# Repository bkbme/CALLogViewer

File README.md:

CALLogViewer
============

A remote logviewer.

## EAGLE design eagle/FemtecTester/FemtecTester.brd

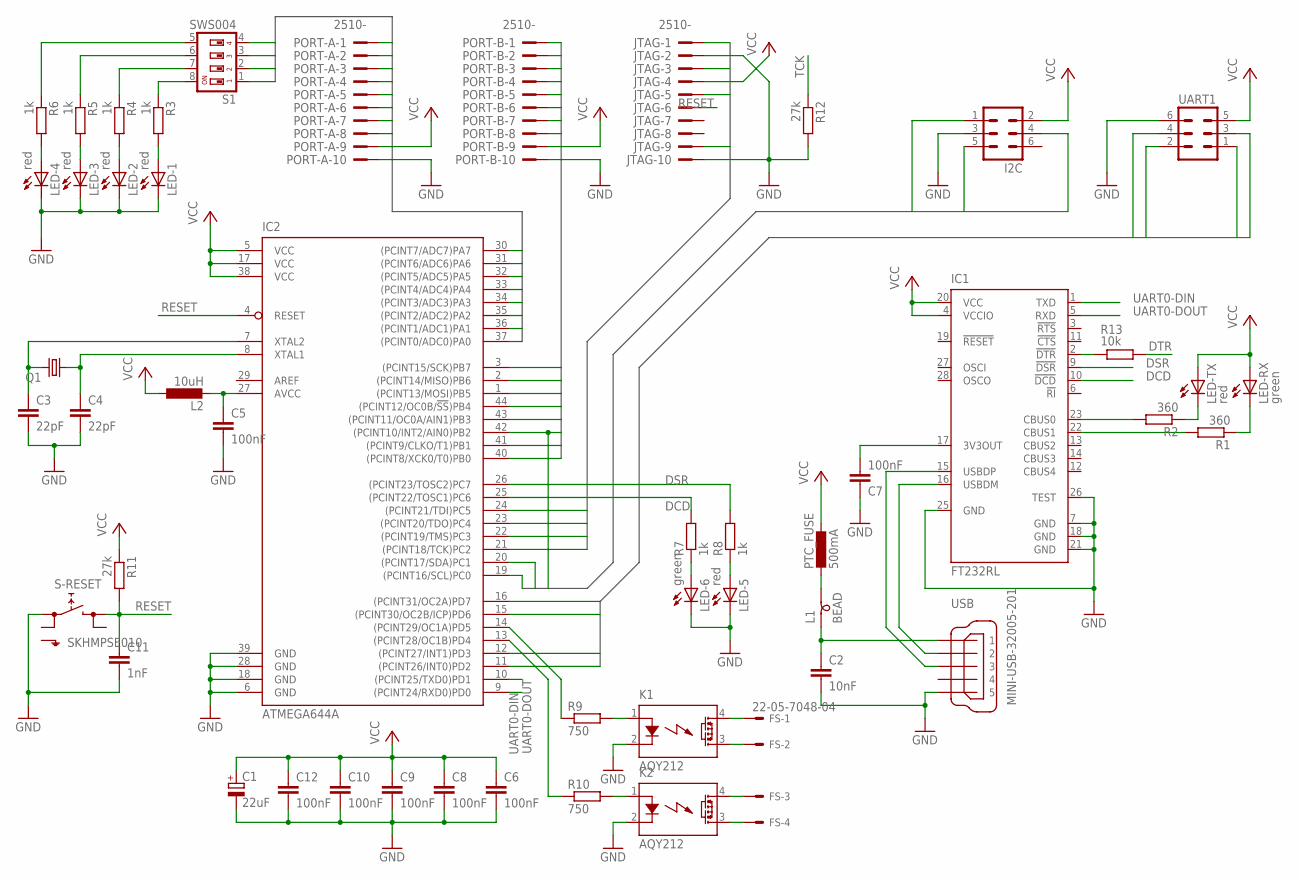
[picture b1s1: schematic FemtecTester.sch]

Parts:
C1: 22uF; SMC_D
C2: 10nF; C1206K
C3, C4: 22pF; C1206K
C5, C6, C7, C8, C9, C10, C12: 100nF; C1206K
C11: 1nF; C1206K
FS: 22-05-7048-04; 7395-04
I2C: ML6
IC1: FT232RL; SSOP28
IC2: ATMEGA644A; TQFP44
JTAG: 2510-; PAK100/2500-10
K1, K2: AQY212; SMD-DIP04
L1: BEAD; SM-B9
L2: 10uH; L3230M
LED-1, LED-2, LED-3, LED-4, LED-5: red; CHIPLED_1206
LED-6: green; CHIPLED_1206
LED-RX: green; CHIPLED_1206
LED-TX: red; CHIPLED_1206
PORT-A: 2510-; PAK100/2500-10
PORT-B: 2510-; PAK100/2500-10
PTC_FUSE: 500mA; L1812
Q1: CRYSTALHC49UP; HC49UP
R1, R2: 360; M1206
R3, R4, R5, R6, R7, R8: 1k; M1206
R9, R10: 750; M1206
R11, R12: 27k; M1206
R13: 10k; M1206
S1: SWS004; SMS-004
S-RESET: SKHMPSE010; SKHMPXE010
UART1: ML6
USB: MINI-USB-32005-201; 32005-201

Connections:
A0: IC2.37 ((PCINT0/ADC0)PA0), PORT-A.1
A1: IC2.36 ((PCINT1/ADC1)PA1), PORT-A.2
A2: IC2.35 ((PCINT2/ADC2)PA2), PORT-A.3
A3: IC2.34 ((PCINT3/ADC3)PA3), PORT-A.4
A4: IC2.33 ((PCINT4/ADC4)PA4), PORT-A.5, S1.1
A5: IC2.32 ((PCINT5/ADC5)PA5), PORT-A.6, S1.2
A6: IC2.31 ((PCINT6/ADC6)PA6), PORT-A.7, S1.3
A7: IC2.30 ((PCINT7/ADC7)PA7), PORT-A.8, S1.4
B0: IC2.40 ((PCINT8/XCK0/T0)PB0), PORT-B.1
B1: IC2.41 ((PCINT9/CLKO/T1)PB1), PORT-B.2
B2/INT: I2C.5, IC2.42 ((PCINT10/INT2/AIN0)PB2), PORT-B.3
B3: IC2.43 ((PCINT11/OC0A/AIN1)PB3), PORT-B.4
B4: IC2.44 ((PCINT12/OC0B/!SS!)PB4), PORT-B.5
B5: IC2.1 ((PCINT13/MOSI)PB5), PORT-B.6
B6: IC2.2 ((PCINT14/MISO)PB6), PORT-B.7
B7: IC2.3 ((PCINT15/SCK)PB7), PORT-B.8
CTS: IC2.16 ((PCINT31/OC2A)PD7), UART1.3
DCD: IC1.10 (!DCD), IC2.25 ((PCINT22/TOSC1)PC6), R7.2
DSR: IC1.9 (!DSR), IC2.26 ((PCINT23/TOSC2)PC7), R8.2
DTR: IC2.15 ((PCINT30/OC2B/ICP)PD6), R13.1, UART1.4
GND: C1.-, C2.2, C3.2, C4.2, C5.2, C6.2, C7.2, C8.2, C9.2, C10.2, C11.2, C12.2, I2C.3, IC1.7 (GND), IC1.18 (GND), IC1.21 (GND), IC1.25 (GND), IC1.26 (TEST), IC2.6 (GND), IC2.18 (GND), IC2.28 (GND), IC2.39 (GND), JTAG.2, JTAG.10, K1.2 (K), K2.2 (K), LED-1.C, LED-2.C, LED-3.C, LED-4.C, LED-5.C, LED-6.C, PORT-A.10, PORT-B.10, R12.2, S-RESET.1 (1.1), UART1.6, USB.5
unnamed: IC1.16 (USBDM), USB.2
unnamed: C3.1, IC2.7 (XTAL2), Q1.2
unnamed: IC1.15 (USBDP), USB.3
unnamed: C5.1, IC2.27 (AVCC), L2.2
unnamed: C4.1, IC2.8 (XTAL1), Q1.1
unnamed: C2.1, L1.1, USB.1
unnamed: C7.1, IC1.17 (3V3OUT)
unnamed: R3.1, S1.8
unnamed: R4.1, S1.7
unnamed: IC1.23 (CBUS0), R2.2
unnamed: IC1.22 (CBUS1), R1.2
unnamed: LED-TX.C, R2.1
unnamed: LED-RX.C, R1.1
unnamed: R5.1, S1.6
unnamed: R6.1, S1.5
unnamed: LED-4.A, R6.2
unnamed: LED-3.A, R5.2
unnamed: LED-2.A, R4.2
unnamed: LED-1.A, R3.2
unnamed: IC2.13 ((PCINT28/OC1B)PD4), R10.1
unnamed: LED-6.A, R7.1
unnamed: LED-5.A, R8.1
unnamed: IC2.14 ((PCINT29/OC1A)PD5), R9.1
unnamed: FS.2, K1.3 (DS2)
unnamed: FS.1, K1.4 (DS1)
unnamed: K1.1 (A), R9.2
unnamed: K2.1 (A), R10.2
unnamed: L1.2, PTC_FUSE.2
unnamed: FS.3, K2.4 (DS1)
unnamed: FS.4, K2.3 (DS2)
unnamed: IC1.2 (!DTR), R13.2
RESET: C11.1, IC2.4 (RESET), JTAG.6, R11.2, S-RESET.3 (2.1)
RX: IC2.11 ((PCINT26/INT0)PD2), UART1.1
SCL: I2C.4, IC2.19 ((PCINT16/SCL)PC0)
SDA: I2C.1, IC2.20 ((PCINT17/SDA)PC1)
TCK: IC2.21 ((PCINT18/TCK)PC2), JTAG.1, R12.1
TDI: IC2.24 ((PCINT21/TDI)PC5), JTAG.9
TDO: IC2.23 ((PCINT20/TDO)PC4), JTAG.3
TMS: IC2.22 ((PCINT19/TMS)PC3), JTAG.5
TX: IC2.12 ((PCINT27/INT1)PD3), UART1.2
UART0-DIN: IC1.1 (TXD), IC2.9 ((PCINT24/RXD0)PD0)
UART0-DOUT: IC1.5 (RXD), IC2.10 ((PCINT25/TXD0)PD1)
VCC: C1.+, C6.1, C8.1, C9.1, C10.1, C12.1, I2C.2, IC1.4 (VCCIO), IC1.20 (VCC), IC2.5 (VCC), IC2.17 (VCC), IC2.38 (VCC), JTAG.4, L2.1, LED-RX.A, LED-TX.A, PORT-A.9, PORT-B.9, PTC_FUSE.1, R11.1, UART1.5

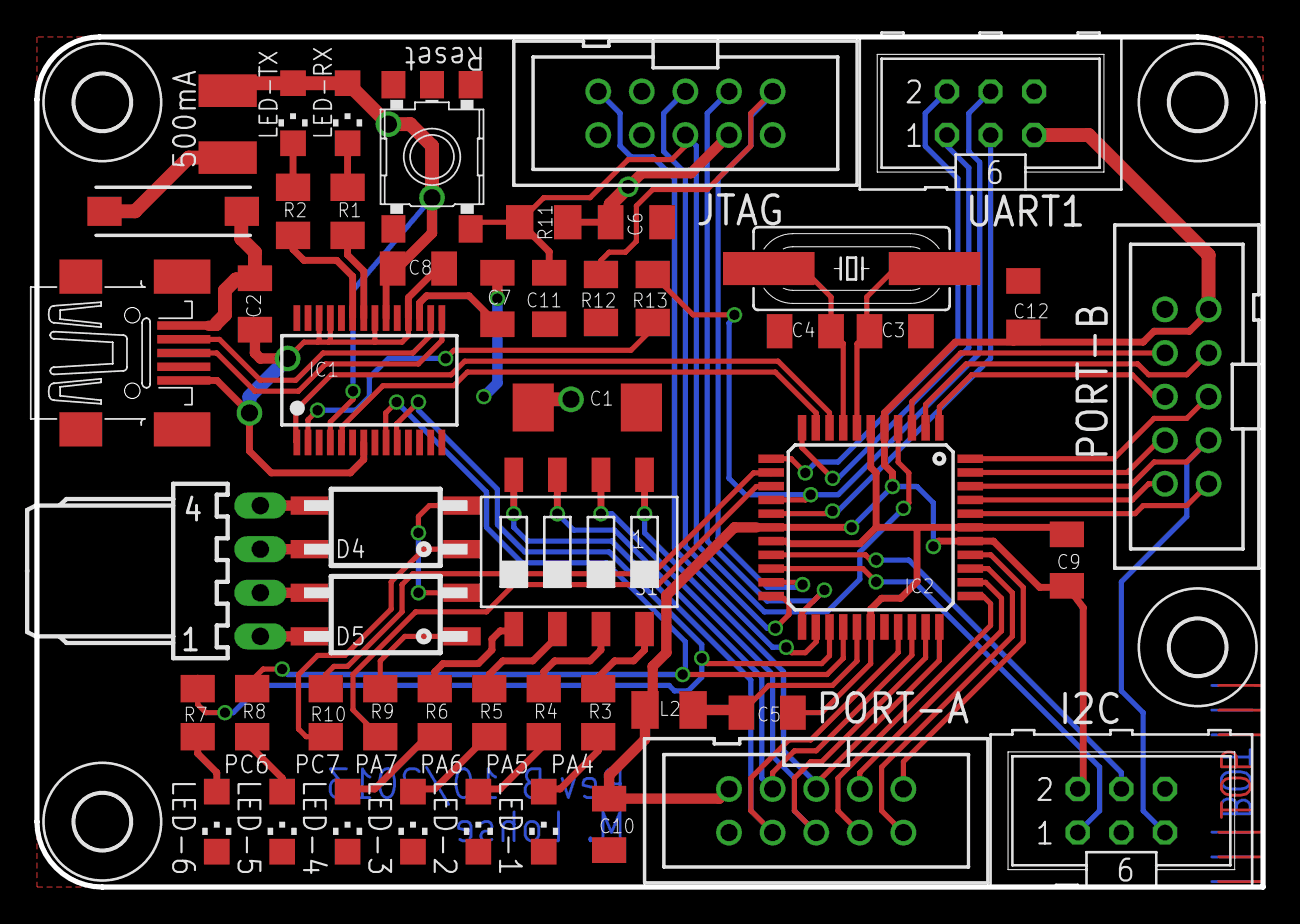
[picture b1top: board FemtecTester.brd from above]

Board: 2 copper layers, 71.4 x 49.5 mm, 54 parts (0 on the bottom side), 64 nets.

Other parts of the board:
U$1, U$2, U$3, U$4: 3,2

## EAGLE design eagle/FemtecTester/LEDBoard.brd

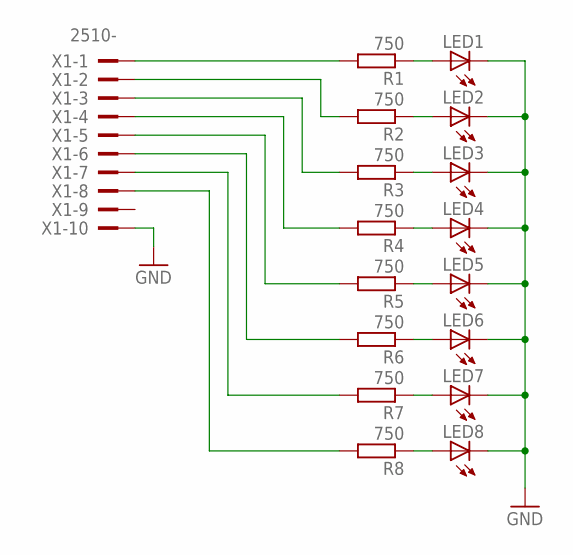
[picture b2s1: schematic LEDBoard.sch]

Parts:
LED1, LED2, LED3, LED4, LED5, LED6, LED7, LED8: LED3MM
R1, R2, R3, R4, R5, R6, R7, R8: 750; R1206
X1: 2510-; PAK100/2500-10

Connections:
GND: LED1.K (C), LED2.K (C), LED3.K (C), LED4.K (C), LED5.K (C), LED6.K (C), LED7.K (C), LED8.K (C), X1.10
unnamed: R1.2, X1.1
unnamed: R2.2, X1.2
unnamed: R3.2, X1.3
unnamed: R4.2, X1.4
unnamed: R5.2, X1.5
unnamed: R6.2, X1.6
unnamed: R7.2, X1.7
unnamed: R8.2, X1.8
unnamed: LED1.A, R1.1
unnamed: LED2.A, R2.1
unnamed: LED3.A, R3.1
unnamed: LED4.A, R4.1
unnamed: LED5.A, R5.1
unnamed: LED6.A, R6.1
unnamed: LED7.A, R7.1
unnamed: LED8.A, R8.1

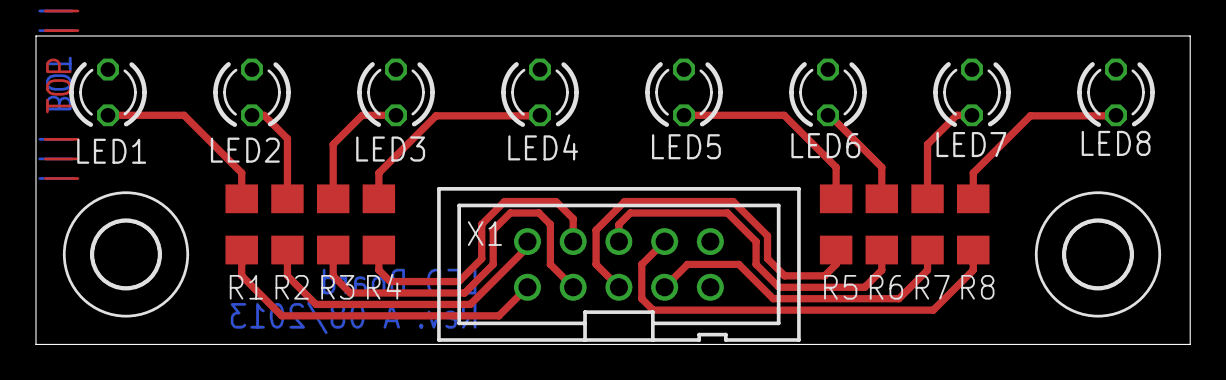
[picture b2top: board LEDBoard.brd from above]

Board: 2 copper layers, 64.1 x 17.1 mm, 19 parts (0 on the bottom side), 17 nets.

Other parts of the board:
U$1, U$2: 3,6

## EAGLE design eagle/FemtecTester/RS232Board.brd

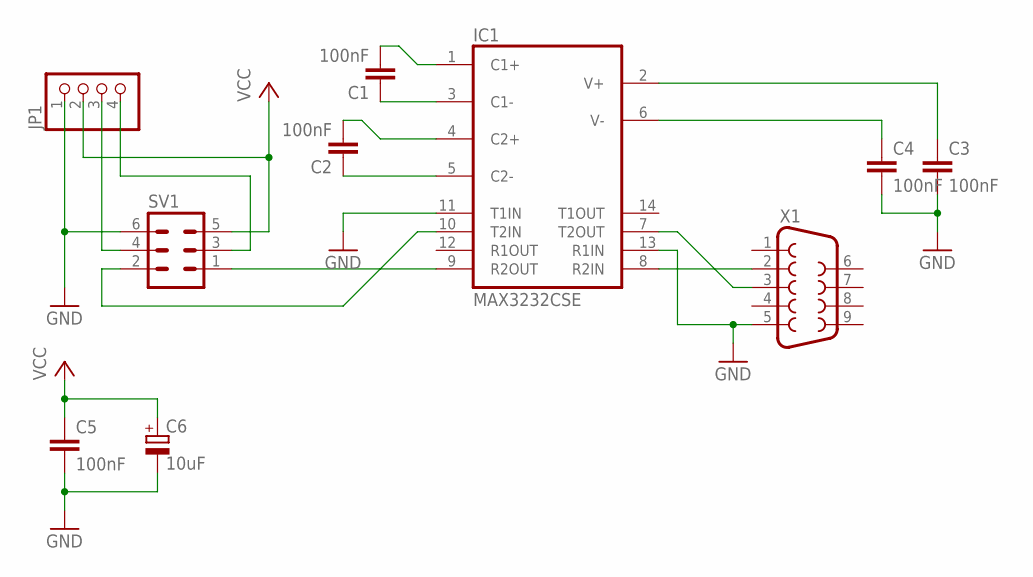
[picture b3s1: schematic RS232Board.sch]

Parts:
C1, C2, C3, C4, C5: 100nF; C1206
C6: 10uF; SMC_C
IC1: MAX3232CSE; SO16
JP1: PINHD-1X4; 1X04
SV1: ML6
X1: F09HP

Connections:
GND: C3.2, C4.2, C5.2, C6.-, IC1.11 (T1IN), IC1.13 (R1IN), IC1.15 (GND), JP1.1, SV1.6, X1.5
unnamed: IC1.8 (R2IN), X1.2
unnamed: IC1.7 (T2OUT), X1.3
unnamed: C2.1, IC1.5 (C2-)
unnamed: C2.2, IC1.4 (C2+)
unnamed: C1.1, IC1.3 (C1-)
unnamed: C1.2, IC1.1 (C1+)
unnamed: C4.1, IC1.6 (V-)
unnamed: C3.1, IC1.2 (V+)
unnamed: JP1.3, SV1.4
unnamed: IC1.9 (R2OUT), SV1.1
unnamed: IC1.10 (T2IN), SV1.2
unnamed: JP1.4, SV1.3
VCC: C5.1, C6.+, IC1.16 (VCC), JP1.2, SV1.5

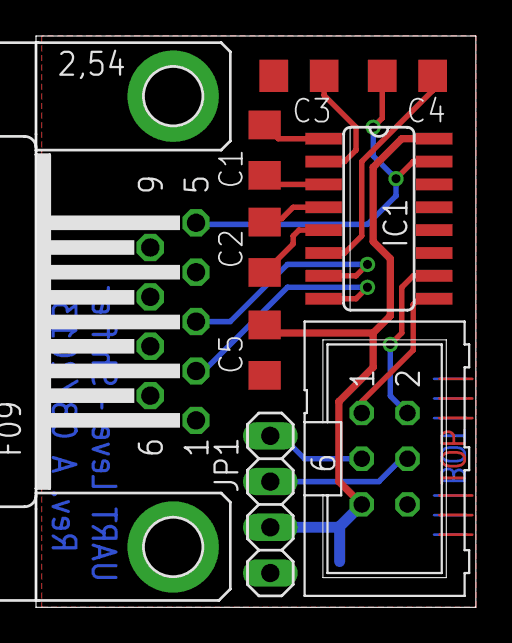
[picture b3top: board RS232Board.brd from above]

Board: 2 copper layers, 24.4 x 31.7 mm, 10 parts (1 on the bottom side), 14 nets.

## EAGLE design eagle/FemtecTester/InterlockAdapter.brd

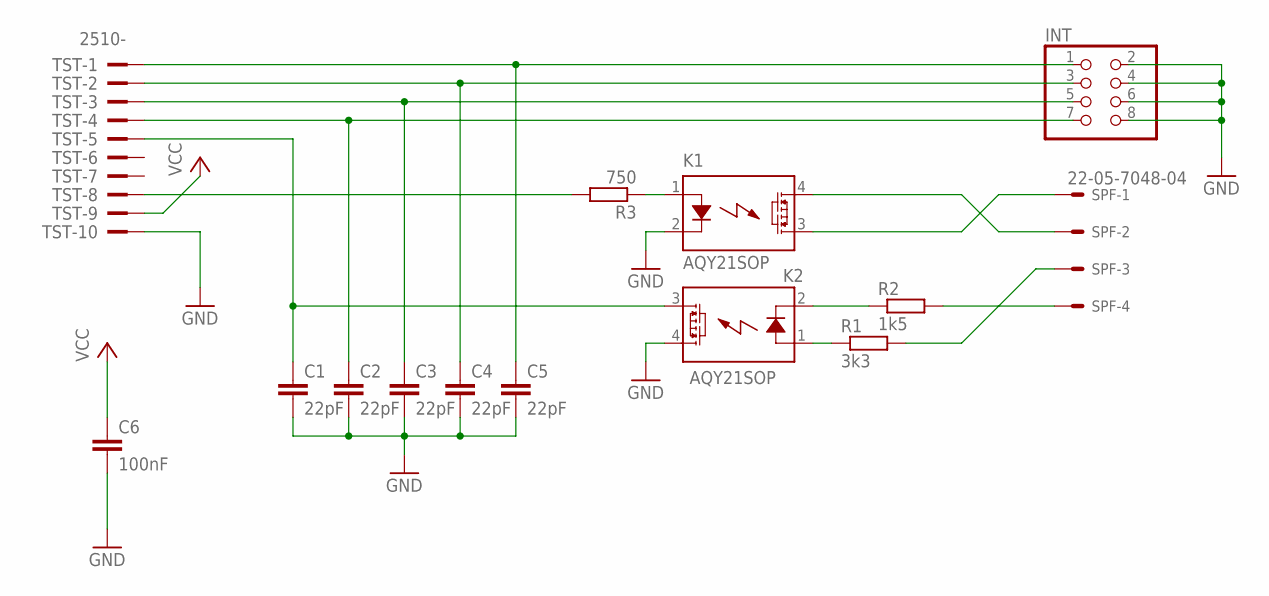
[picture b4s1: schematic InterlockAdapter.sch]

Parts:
C1, C2, C3, C4, C5: 22pF; C1206K
C6: 100nF; C1206K
INT: PINHD-2X4/90; 2X04/90
K1, K2: AQY21SOP; SOP04
R1: 3k3; R1206
R2: 1k5; R1206
R3: 750; R1206
SPF: 22-05-7048-04; 7395-04
TST: 2510-; PAK100/2500-10

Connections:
GND: C1.2, C2.2, C3.2, C4.2, C5.2, C6.2, INT.2, INT.4, INT.6, INT.8, K1.2 (K), K2.4 (DS1), TST.10
unnamed: C5.1, INT.1, TST.1
unnamed: C4.1, INT.3, TST.2
unnamed: C3.1, INT.5, TST.3
unnamed: C2.1, INT.7, TST.4
unnamed: C1.1, K2.3 (DS2), TST.5
unnamed: K2.2 (K), R2.1
unnamed: K2.1 (A), R1.1
unnamed: K1.3 (DS2), SPF.1
unnamed: K1.4 (DS1), SPF.2
unnamed: R2.2, SPF.4
unnamed: R1.2, SPF.3
unnamed: K1.1 (A), R3.1
unnamed: R3.2, TST.8
VCC: C6.1, TST.9

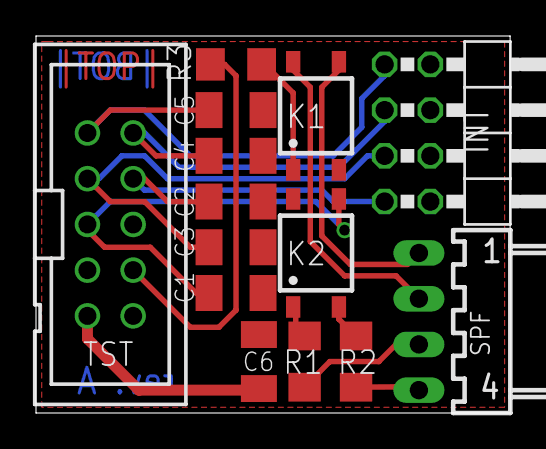
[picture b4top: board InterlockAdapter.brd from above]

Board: 2 copper layers, 26.3 x 20.9 mm, 14 parts (0 on the bottom side), 15 nets.

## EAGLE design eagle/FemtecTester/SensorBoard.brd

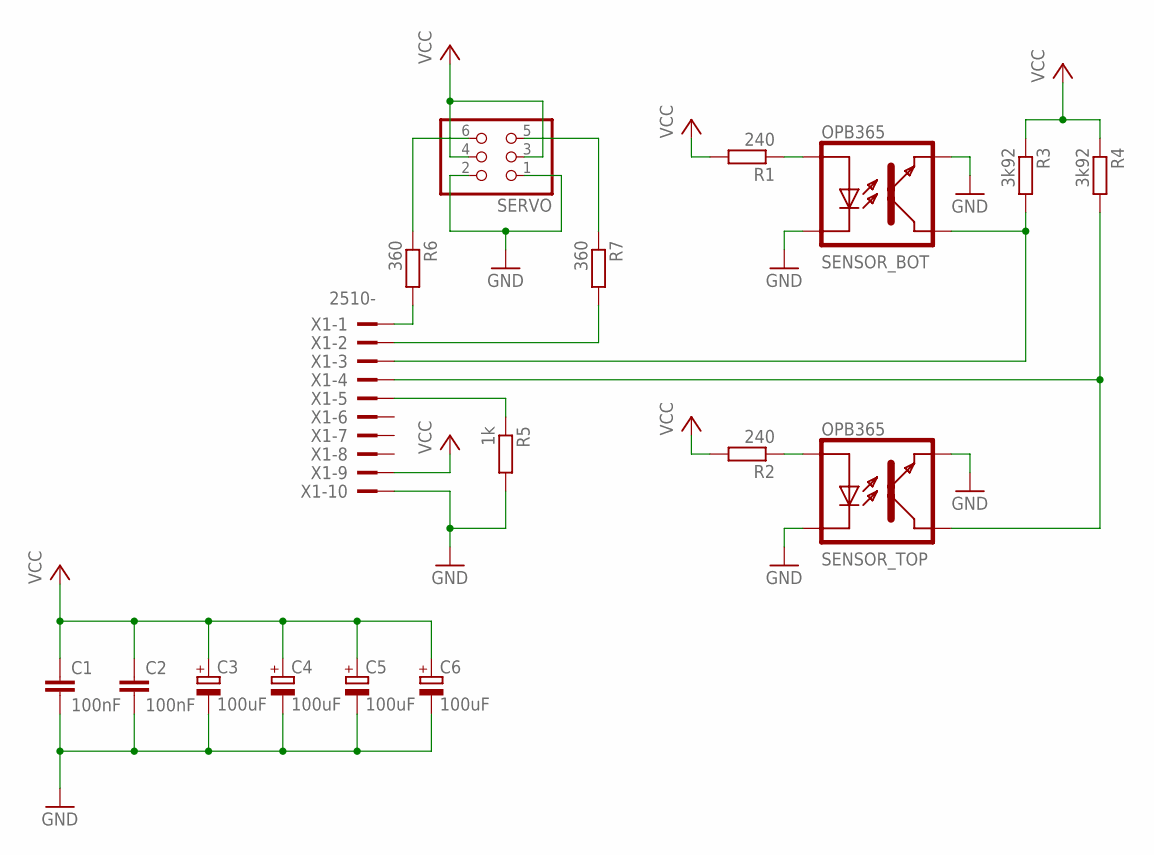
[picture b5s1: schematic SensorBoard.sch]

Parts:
C1, C2: 100nF; C1206
C3, C4, C5, C6: 100uF; SMC_D
R1, R2: 240; R1206
R3, R4: 3k92; R1206
R5: 1k; R1206
R6, R7: 360; R1206
SENSOR_BOT: OPB365T; OPB365-T
SENSOR_TOP: OPB365T; OPB365-T
SERVO: PINHD-2X3/90; 2X03/90
X1: 2510-; PAK100/2500-10

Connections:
GND: C1.2, C2.2, C3.-, C4.-, C5.-, C6.-, R5.2, SENSOR_BOT.2, SENSOR_BOT.4, SENSOR_TOP.2, SENSOR_TOP.4, SERVO.1, SERVO.2, X1.10
unnamed: R2.1, SENSOR_TOP.1
unnamed: R1.1, SENSOR_BOT.1
unnamed: R4.2, SENSOR_TOP.3, X1.4
unnamed: R3.2, SENSOR_BOT.3, X1.3
unnamed: R5.1, X1.5
unnamed: R6.1, SERVO.6
unnamed: R7.2, X1.2
unnamed: R6.2, X1.1
unnamed: R7.1, SERVO.5
VCC: C1.1, C2.1, C3.+, C4.+, C5.+, C6.+, R1.2, R2.2, R3.1, R4.1, SERVO.3, SERVO.4, X1.9

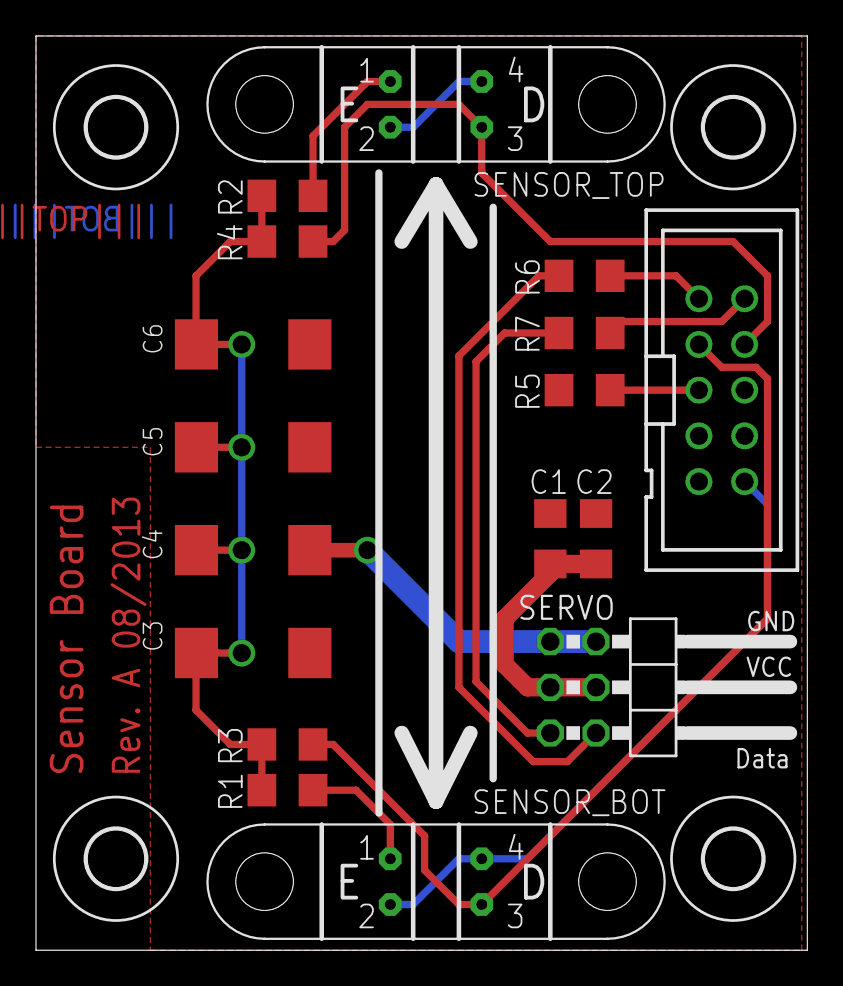
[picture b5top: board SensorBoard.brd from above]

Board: 2 copper layers, 42.9 x 50.8 mm, 21 parts (0 on the bottom side), 11 nets.

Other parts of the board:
U$1, U$2, U$3, U$4: 3,2

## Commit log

2012-06-14 Initial Checkin.
2012-06-14 Added default values when reading settings.
2012-06-14 Removed user project file from git.
2012-06-14 Removed 7z resource files.
2012-06-14 several small bugfixes, allow support_info files to be opened on Windows
2012-06-14 Add windows tools for extrating gzipped tar archives
2012-06-14 add service tool buttons for Dragan
2012-06-15 Partial implementation of log facility distinction.
2012-06-15 nolog
2012-06-15 Added drop support for supportInfo into logView.
2012-09-04 add FemtecTester (procedure footswitch simulator) and icons for tool buttons etc.
2012-09-04 fix timer interval
2013-03-11 Add session support, replace text-highlighting in LogView with real search function, add settings dialog, add zap-option for cal (services menu), some other refactoring...
2013-03-11 remove unused icons
2013-03-12 add new icons and tooltips for session view
2013-03-12 add about dialog
2013-03-12 add icon for tester settings page
2013-03-12 fix build errors on Windows
2013-03-13 fix tooltips for CAL exit codes in session view
2013-03-13 set title for support info file dialog
2013-03-13 enable web-inspector for development builds only
2013-03-13 load page settings when page is added to settings dialog
2013-03-13 add general settings page and auto connect
2013-03-14 improve settings dialog size
2013-04-10 replace old footswitch simulator with FemtoTester (experimental)
2013-04-10 fix endless loop connecting FemtoTester
2013-04-10 upgrade to QextSerialPort-1.2RC
2013-04-10 Fix build error and bug writing to serial port on Windows
2013-04-11 change labels for FemtoTester
2013-04-12 add statusbar widget for FemtoTester
2013-04-12 fix statusbar messages for procedure footswitch
2013-04-15 Add DockingForceMessage
2013-04-15 fix some bugs due to missing casts
2013-04-16 add DockingLimitMessage and ServoCtrlMessage
2013-04-16 fix timeout for status message
2013-04-16 remove dependency for endian.h
2013-04-18 release procedure footswitch when powercheck finishes
2013-04-19 add settings page for dock (experimental)
2013-04-24 add auto-dock and improve dock settings page
2013-04-24 lock dock when treatment starts
2013-04-24 restore settings for current page only
2013-04-24 display z-force and ref voltage in tester status widget
2013-04-25 add dock buttons to mainwindow
2013-04-25 undock on dms reset
2013-04-26 fix bug parsing warning messages
2013-05-08 Replace FSR sensor with Kern PCB-10000-1, add tare and docking state messages
2013-05-08 add tooltips for dock buttons
2013-05-10 add application icon, dock icon and update tester icon
2013-05-10 improve app icon
2013-05-10 add rc-file for Windows application icon
2013-05-10 add firmware for FemtoTester
2013-05-21 ignore CALLogView.pro.user
2013-05-21 improve application icon for windows
2013-06-21 add API description for FemtoTester firmware
2013-07-01 fix bug parsing error message
2013-07-01 inject log messages for procedure footswitch states from FemtoTester
2013-07-01 add docking slot support (requires firmware-update\!)
2013-07-03 increment minor version (v1.3)
2013-07-09 add femto tester protocol version to about dialog
2013-08-05 Added last state of FemtoTester to QSettings. Only read the last state of the FemtoTester from QSettings if enviroment variable AUTOCONNECT_FEMTOTESTER is set (to any value).
2013-08-06 Changed minor version to 4.
2013-09-05 modifications for new dock
2013-09-05 correct status message
2013-09-16 Release 1.5 for G+ (dock buttons/settings hidden by default)
2013-09-18 Bugfixes for servo control and some other minor firmware issues
2013-09-18 version bump: 1.6 beta
2013-09-20 add eagle files to git repository
2013-10-01 fix message checksum calculation bug
2013-10-04 introduce build targets for dock/footswitch
2013-10-04 fix footswitch led status
2013-11-28 clean up code and update settings for prototype docking table
2013-11-28 fix broken file (missing code)
2013-11-28 extend version message by build target
2013-12-13 add readme for building and programming firmware
2013-12-16 introduce limit for number of log messages loaded per session (configurable by user)
2013-12-17 increment version number and fix compiler warnings (remove leftovers from refactored code)
2014-01-08 use message identifiers from MessageParser
2014-01-10 show dock settings when dock is detected, cleanup application shutdown
2014-01-10 store docking slot positions and servo speeds in eeprom -> new protocol version
2014-01-14 store docking limits in eeprom
2014-01-14 emit settingsArrayChanged() signal when array is stored successfully
2014-01-16 set default target: VICTUS_DOCK_TARGET
2014-01-17 make destructor of class AbstractMessage virtual
2014-01-20 add missing settings.c/h
2014-03-02 update FemtoTester eagle files (rev. B)
